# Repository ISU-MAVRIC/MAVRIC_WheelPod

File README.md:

MAVRIC_WheelPod
===============

Each MAVRIC Wheel Pod contains a motor controller driving the wheel along with a stepper to rotate the entire pod, steering the rover. This board controls these components in a compact, modular form factor. One will be located at each of the six wheel pods.

**Features:**
- STM32F4 Microcontroller
- PWM output to motor driver controlling wheel speed
- Current measurement on motor driver to measure wheel traction
- Stepper motor output to rotate the wheel pod, steering the rover
- Encoder analog in for steering position feedback, fed into a control loop
- RJ45 Jack for rx/tx control/status data as well as powering the wheel pod's 3V3 and 5V rails

##PCB Progress:
### Wheel Pod Board v1.0 ordered!
https://github.com/ISU-MAVRIC/MAVRIC_WheelPod/releases/tag/v1.0

Current Price: $12.60 for 3 boards, $4.20 each

<br>

### Grid Settings
- .5mm layout
- .5mm traces when possible, down to .25mm for detailed routing

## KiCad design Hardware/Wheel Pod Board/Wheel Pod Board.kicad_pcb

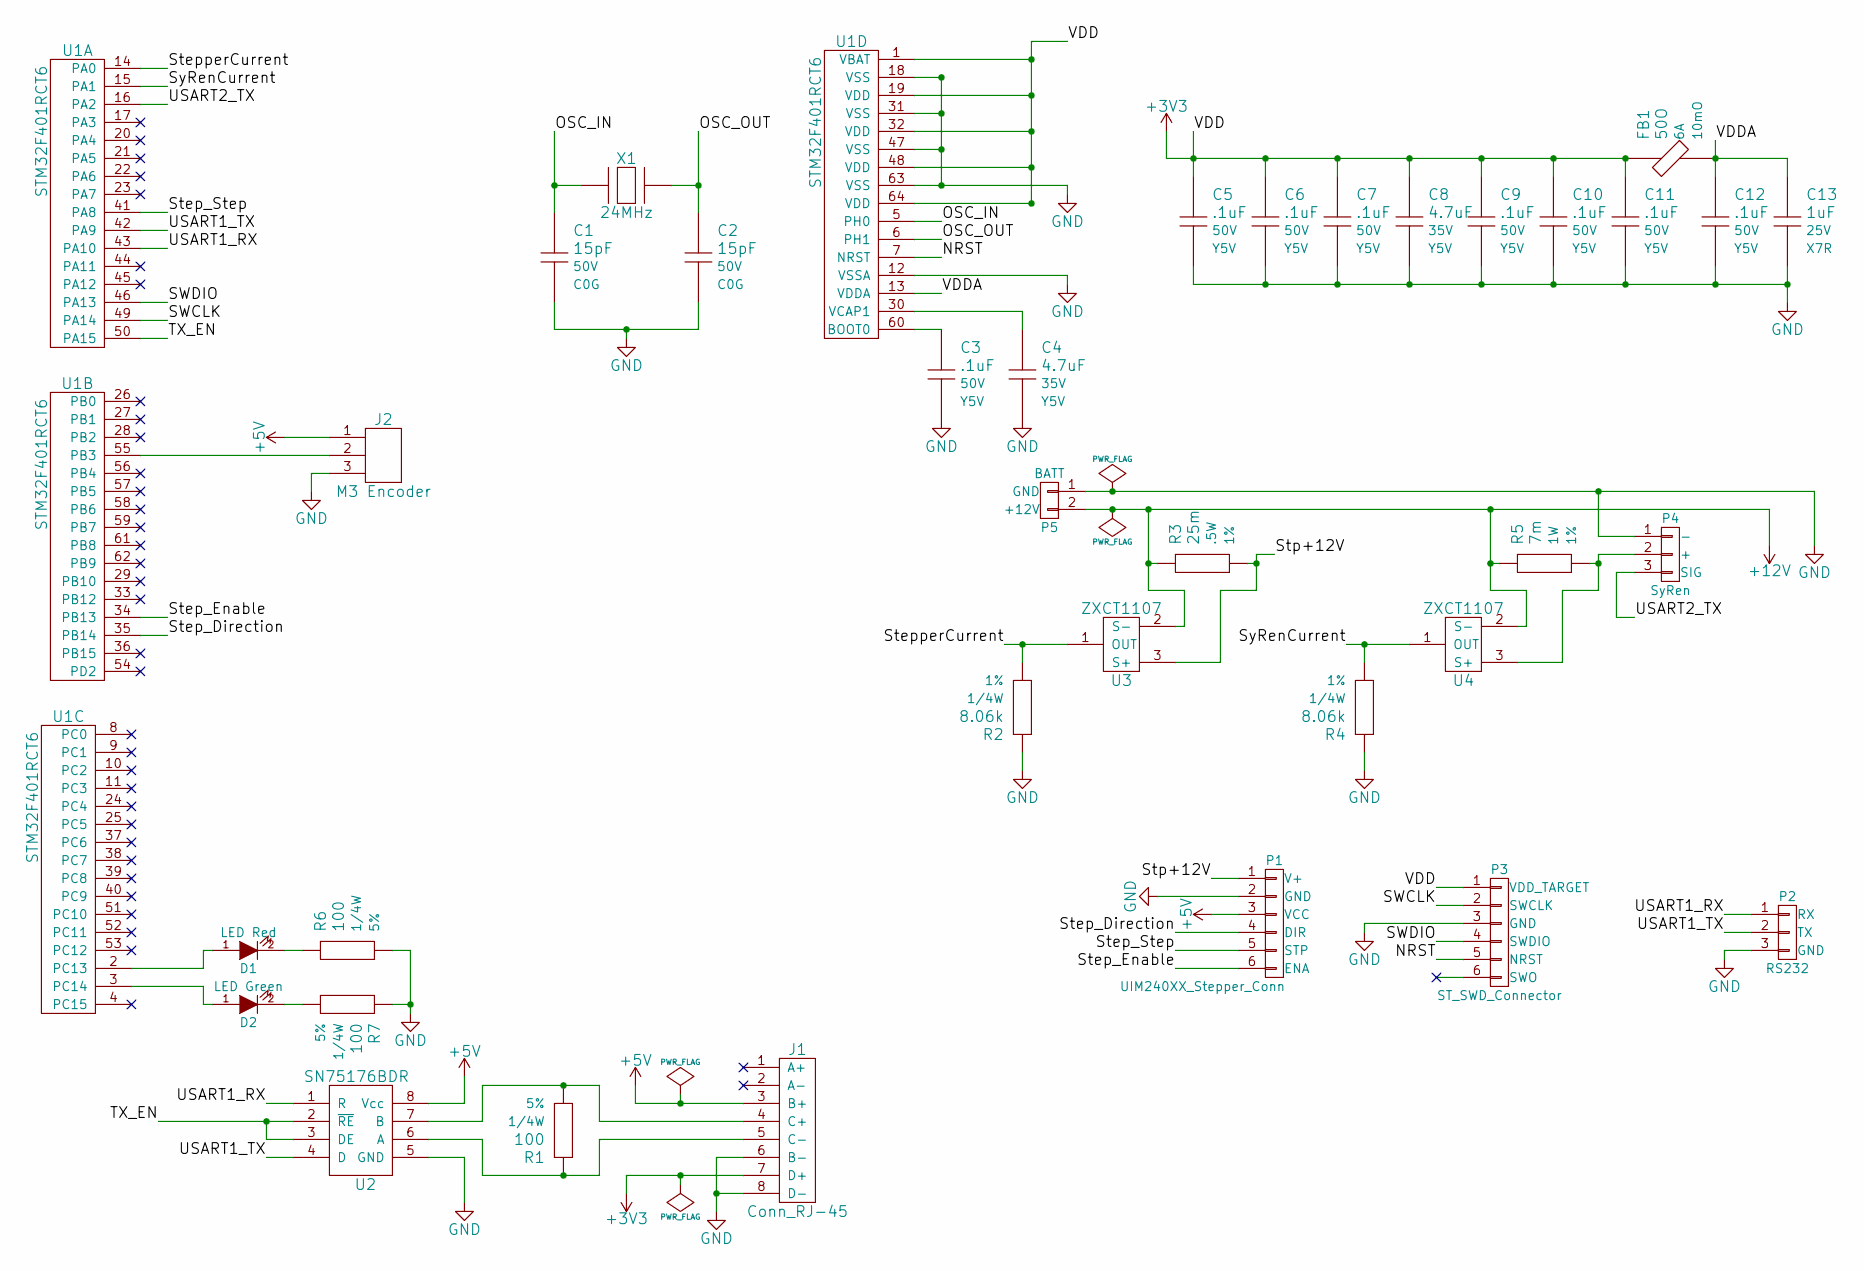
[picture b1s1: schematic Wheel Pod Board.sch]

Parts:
C1, C2: 15pF; C_1206_HandSoldering; Voltage 50V; Manufacturer Part # CL31C150JBCNNNC
C3, C5, C6, C7, C9, C10, C11, C12: .1uF; C_1206_HandSoldering; Voltage 50V; Manufacturer Part # CL31F104MBCNNNC
C4, C8: 4.7uF; C_1206_HandSoldering; Voltage 35V; Manufacturer Part # GMK316F475ZG-T
C13: 1uF; C_1206_HandSoldering; Voltage 25V; Manufacturer Part # C1206C105M3RACTU
D1: LED Red; R_0805_HandSoldering
D2: LED Green; R_0805_HandSoldering
FB1: 50O; R_1206_HandSoldering; Manufacturer Part # HI1206T500R-10
J1: Conn_RJ-45; Molex_RJ45_0437438101
J2: M3 Encoder; SolderWirePad_3x_0-8mmDrill
P1: UIM240XX_Stepper_Conn; 1x6_Breakaway_Header
P2: RS232; 1x3_Breakaway_Header
P3: ST_SWD_Connector; 1x6_Breakaway_Header
P4: SyRen; SolderWirePad_3x_0-8mmDrill
P5: BATT; SolderWirePad_2x_0-8mmDrill
R1, R6, R7: 100; R_1206_HandSoldering; Tolerance 5%; Manufacturer Part # ERJ-8GEYJ101V
R2, R4: 8.06k; R_1206_HandSoldering; Tolerance 1%; Manufacturer Part # ERJ-8ENF8061V
R3: 25m; R_1206_HandSoldering; Tolerance 1%; Manufacturer Part # LRC-LRF1206LF-01-R025F
R5: 7m; R_1206_HandSoldering; Tolerance 1%; Manufacturer Part # CSR1206-0R007F1
U1: STM32F401RCT6; LQFP-64_10x10mm_Pitch0.5mm
U2: SN75176BDR; SOIC-8_3.9x4.9mm_Pitch1.27mm
U3, U4: ZXCT1107; SOT23_Handsoldering
X1: 24MHz; Q_49U3HMS; Tolerance 30ppm; Manufacturer Part # 9C-24.000MAAE-T; Digi-Key Value

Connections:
+3V3: C5.1, C6.1, C7.1, C8.1, C9.1, C10.1, C11.1, FB1.1, J1.7 (D+), P3.1 (VDD_TARGET), U1.1 (VBAT), U1.19 (VDD), U1.32 (VDD), U1.48 (VDD), U1.64 (VDD)
+5V: J1.3 (B+), J2.1, P1.3 (VCC), U2.8 (Vcc)
+12V: P5.2 (+12V), R3.1, R5.1, U3.2 (S-), U4.2 (S-)
/NRST: P3.5 (NRST), U1.7 (NRST)
/OSC_IN: C1.1, U1.5 (PH0), X1.1
/OSC_OUT: C2.1, U1.6 (PH1), X1.2
/SWCLK: P3.2 (SWCLK), U1.49 (PA14)
/SWDIO: P3.4 (SWDIO), U1.46 (PA13)
/Step_Direction: P1.4 (DIR), U1.35 (PB14)
/Step_Enable: P1.6 (ENA), U1.34 (PB13)
/Step_Step: P1.5 (STP), U1.41 (PA8)
/StepperCurrent: R2.2, U1.14 (PA0), U3.1 (OUT)
/Stp+12V: P1.1 (V+), R3.2, U3.3 (S+)
/SyRenCurrent: R4.2, U1.15 (PA1), U4.1 (OUT)
/TX_EN: U1.50 (PA15), U2.2 (~RE), U2.3 (DE)
/USART1_RX: P2.1 (RX), U1.43 (PA10), U2.1 (R)
/USART1_TX: P2.2 (TX), U1.42 (PA9), U2.4 (D)
/USART2_TX: P4.3 (SIG), U1.16 (PA2)
/VDDA: C12.1, C13.1, FB1.2, U1.13 (VDDA)
GND: C1.2, C2.2, C3.2, C4.2, C5.2, C6.2, C7.2, C8.2, C9.2, C10.2, C11.2, C12.2, C13.2, J1.6 (B-), J1.8 (D-), J2.3, P1.2 (GND), P2.3 (GND), P3.3 (GND), P4.1 (-), P5.1 (GND), R2.1, R4.1, R6.2, R7.1, U1.12 (VSSA), U1.18 (VSS), U1.31 (VSS), U1.47 (VSS), U1.63 (VSS), U2.5 (GND)
unnamed: C3.1, U1.60 (BOOT0)
unnamed: C4.1, U1.30 (VCAP1)
unnamed: D1.1 (A), U1.2 (PC13)
unnamed: D1.2 (K), R6.1
unnamed: D2.1 (A), U1.3 (PC14)
unnamed: D2.2 (K), R7.2
unnamed: J1.4 (C+), R1.2, U2.7 (B)
unnamed: J1.5 (C-), R1.1, U2.6 (A)
unnamed: J2.2, U1.55 (PB3)
unnamed: P4.2 (+), R5.2, U4.3 (S+)

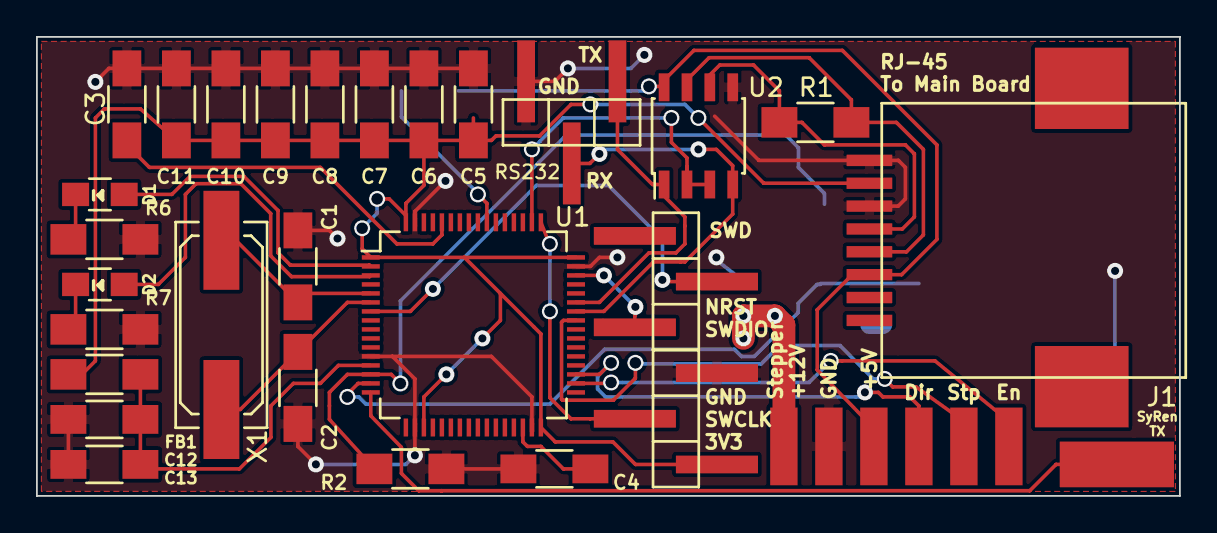
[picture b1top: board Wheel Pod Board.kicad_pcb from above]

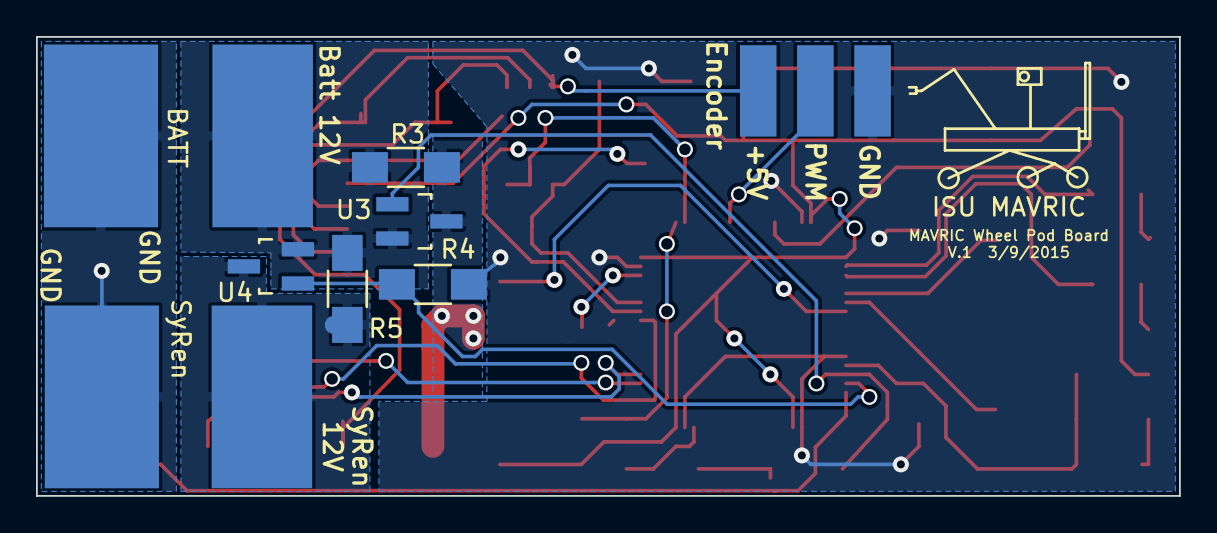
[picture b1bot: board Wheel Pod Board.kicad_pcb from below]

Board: 2 copper layers, 63.5 x 25.5 mm, 36 parts (9 on the bottom side), 30 nets.

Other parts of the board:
ISU MAVRIC: VAL**; MAVRIC_LOGO

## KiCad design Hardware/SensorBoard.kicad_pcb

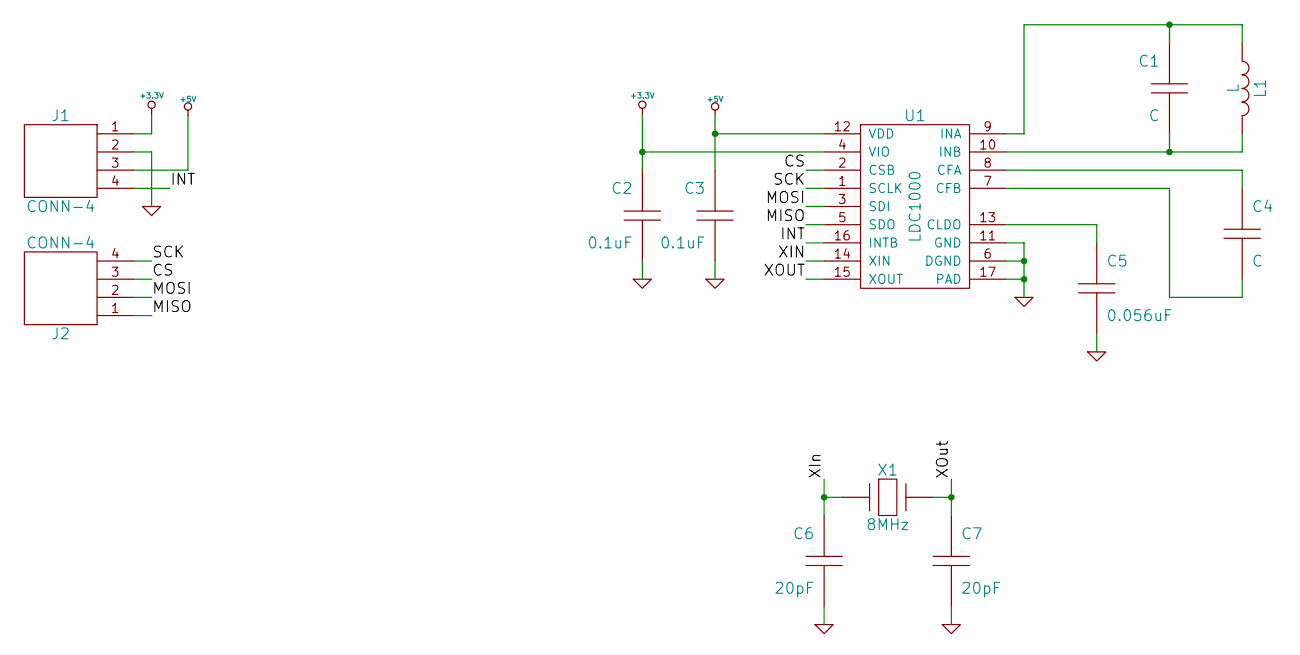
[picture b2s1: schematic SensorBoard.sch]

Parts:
C1, C4: C; Voltage V
C2, C3: 0.1uF; CAPC1608-N; Voltage 16V; MFR Part No CL10B104KO8NNNC
C5: 0.056uF; CAPC1608-N; Voltage 50V; MFR Part No CL10B563KB8SFNC
C6, C7: 20pF; CAPC1608-N; Voltage 100V; MFR Part No GRM1885C2A200JA01D
J1, J2: CONN-4
L1: L
U1: LDC1000
X1: 8MHz; MFR Part No CX5032GB08000H0HEQZ1

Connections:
+3.3V: C2.1, J1.1, U1.4 (VIO)
+5V: C3.1, J1.3, U1.12 (VDD)
/CS: J2.3, U1.2 (CSB)
/INT: J1.4, U1.16 (INTB)
/MISO: J2.1, U1.5 (SDO)
/MOSI: J2.2, U1.3 (SDI)
/SCK: J2.4, U1.1 (SCLK)
/XIN: C6.1, U1.14 (XIN), X1.1
/XOUT: C7.1, U1.15 (XOUT), X1.2
GND: C2.2, C3.2, C5.2, C6.2, C7.2, J1.2, U1.6 (DGND), U1.11 (GND), U1.17 (PAD)
unnamed: C1.2, L1.1, U1.10 (INB)
unnamed: C1.1, L1.2, U1.9 (INA)
unnamed: C4.2, U1.7 (CFB)
unnamed: C4.1, U1.8 (CFA)
unnamed: C5.1, U1.13 (CLDO)

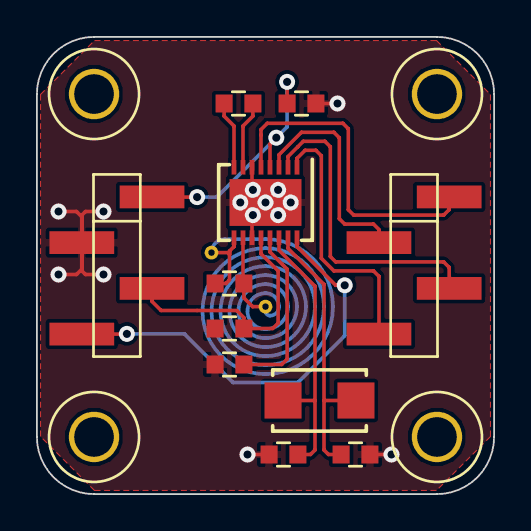
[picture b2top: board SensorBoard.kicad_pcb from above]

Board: 2 copper layers, 25.4 x 25.4 mm, 16 parts (1 on the bottom side), 15 nets.

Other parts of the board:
MECH-HOLE220, MECH-HOLE220#2, MECH-HOLE220#3, MECH-HOLE220#4: VAL**; MECH-HOLE220

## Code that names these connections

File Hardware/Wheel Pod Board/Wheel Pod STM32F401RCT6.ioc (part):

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Mcu.Name=STM32F401R(B-C-D-E)Tx
Mcu.Package=LQFP64
Mcu.UserName=STM32F401RCTx
PA0-WKUP.GPIOParameters=GPIO_Label
PA0-WKUP.GPIO_Label=Stepper Current In
PA0-WKUP.Signal=ADCx_IN0
PA1.GPIOParameters=GPIO_Label
PA1.GPIO_Label=Victor Current In
PA1.Signal=ADCx_IN1
PA10.Mode=Asynchronous
PA10.Signal=USART1_RX
PA13.Mode=Serial-Wire
PA13.Signal=SYS_JTMS-SWDIO
PA14.Mode=Serial-Wire
PA14.Signal=SYS_JTCK-SWCLK
PA15.GPIOParameters=GPIO_Label
PA15.GPIO_Label=485 TX Enable
PA15.Signal=GPIO_Output
PA2.GPIOParameters=GPIO_Label
PA2.GPIO_Label=Victor PWM Out
PA2.Signal=S_TIM5_CH3
PA8.GPIOParameters=GPIO_Label
PA8.GPIO_Label=Stepper Step
PA8.Signal=S_TIM1_CH1
PA9.Mode=Asynchronous
PA9.Signal=USART1_TX
PB13.GPIOParameters=GPIO_Label
PB13.GPIO_Label=Stepper Enable
PB13.Signal=GPIO_Output
PB14.GPIOParameters=GPIO_Label
PB14.GPIO_Label=Stepper Direction
PB14.Signal=GPIO_Output
PB3.GPIOParameters=GPIO_Label
PB3.GPIO_Label=Steering Pos Fdbk PWM In
PB3.Signal=S_TIM2_CH2
PC13-ANTI_TAMP.GPIOParameters=GPIO_Label
PC13-ANTI_TAMP.GPIO_Label=Red LED
PC13-ANTI_TAMP.Signal=GPIO_Output
PC14-OSC32_IN.GPIOParameters=GPIO_Label
PC14-OSC32_IN.GPIO_Label=Green LED
PC14-OSC32_IN.Signal=GPIO_Output
PH0\ -\ OSC_IN.Mode=HSE-External-Oscillator
PH0\ -\ OSC_IN.Signal=RCC_OSC_IN
PH1\ -\ OSC_OUT.Mode=HSE-External-Oscillator
PH1\ -\ OSC_OUT.Signal=RCC_OSC_OUT
RCC.HSE_VALUE=24000000
RCC.SYSCLKFreq_VALUE=84000000
RCC.SYSCLKSource=RCC_SYSCLKSOURCE_PLLCLK

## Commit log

2013-11-16 Create kicad project
2013-11-16 Simple schematic/board for sizing purposes
2013-11-22 Split into separate boards
2013-12-11 Finish Sensor Board
2014-02-06 Added PID Test firmware
2014-02-11 Added PID arm firmware
    Untested code. Currently will convert cartesian commands to polar
    positions and sets PIDs to update to those positions.
2014-02-11 Update variables to match C naming conventions
2014-02-11 Added analog IO test, updated PID_test variables
2014-02-12 PID Output was properly ranged
2014-02-13 Changed file names to be more descriptive
2014-02-14 More test scripts
2014-02-19 Modified for serial motor control
2014-02-22 Tuned PID
2014-03-04 Organized folder
2014-03-04 Added Serial setPoint control
2014-03-06 Tuned PID Coefficients
2014-03-06 Cleaned up code and redid serial communications
2014-03-06 Fixed uninitialized variable
2014-03-11 Primitive parsing for packetized serial
2014-03-13 Motor control commands are now packetized serial
2014-04-24 Changed some variable names for the real life elbow
2014-11-20 Added features list
    Attempt to organize and determine what is possible in our limited space
2014-12-02 WheelPod Power Board Beginnings
    The fumblings of a KiCad rookie made available to the public
2014-12-03 Very Rough Schematic Created
    Just a photo of a pencil drawing, will be drawn digitally soon
2014-12-10 Created MAVRIC part library and new schematic
    New schematic will likely transform into something different in the
    future
2014-12-11 Added LDC to schematic
2015-02-20 Start new schematic and PCB layout
2015-03-05 Import common blocks from Arm Board
2015-03-05 Connect some power, create STMCube project
2015-03-05 Connect current sense, more connectors
    Resistor values not correct #6
    Resolve #2
2015-03-05 Calculate current sense, parts on PCB
    Resolves #6
2015-03-05 More parts on PCB
2015-03-06 Connect 485 to RJ45 jack on schematic
    #5
2015-03-06 Fix footprints, add RJ45 jack to pcb
    Resolve #12, Resolve #5
2015-03-06 Reroute 3V3 and 5V through cat5, remove regs
2015-03-06 Make STM32 connections, fix DRC errors
2015-03-06 Update cube, make connections to microcontroller
2015-03-06 Position components on PCB
    Closes #4
2015-03-06 Begin routing PCB
    Starting #8
2015-03-06 Route all components, generate export + images
    Progressing #8, Close #9 for now
2015-03-06 Add ADC channels to cube, kicad something
2015-03-07 Progress on new pcb route
2015-03-07 Finish PCB reroute one
    Resolve #8, resolve #13
2015-03-07 Attach 485 TX enable to micro
2015-03-07 Fixed SyRen TX pad layers
2015-03-07 Update images to pcb route v2
2015-03-07 Update board price on readme
2015-03-08 Add red and green LEDs to board
2015-03-08 Change out SWD footprint to new breakaway header
2015-03-08 Change 232 header to new breakaway footprint
    what a mess
2015-03-08 Change header footprints to new ones in schematic
    Forgot to save this until now, did this before I made the PCB changes
2015-03-09 Add pads for connecting encoder
    Schematic, PCB, and in cube
    Resolves #16
2015-03-09 Add resistor for green LED, clean up references
2015-03-09 Create BOM, send exports to fab
2015-03-09 Update board images for v1.0 fab
2015-03-09 Update readme for v1.0 board order info
2015-03-11 Fix LED polarity
2015-04-02 Working LED blink test firmware
2015-04-11 Add cube labels, SyRen TX changed to Victor PWM out
2015-04-11 Enable external crystal in cube, export code
2015-04-11 Add some really excellent not working PWM code
    hire me
2015-04-18 Cleanup old projects
2015-04-18 Add wheelpod project with working timers
2015-04-18 Update timer values to match servo pwm period
2015-04-18 Fix pwm out for servo
    Forgot to save before last commit.
